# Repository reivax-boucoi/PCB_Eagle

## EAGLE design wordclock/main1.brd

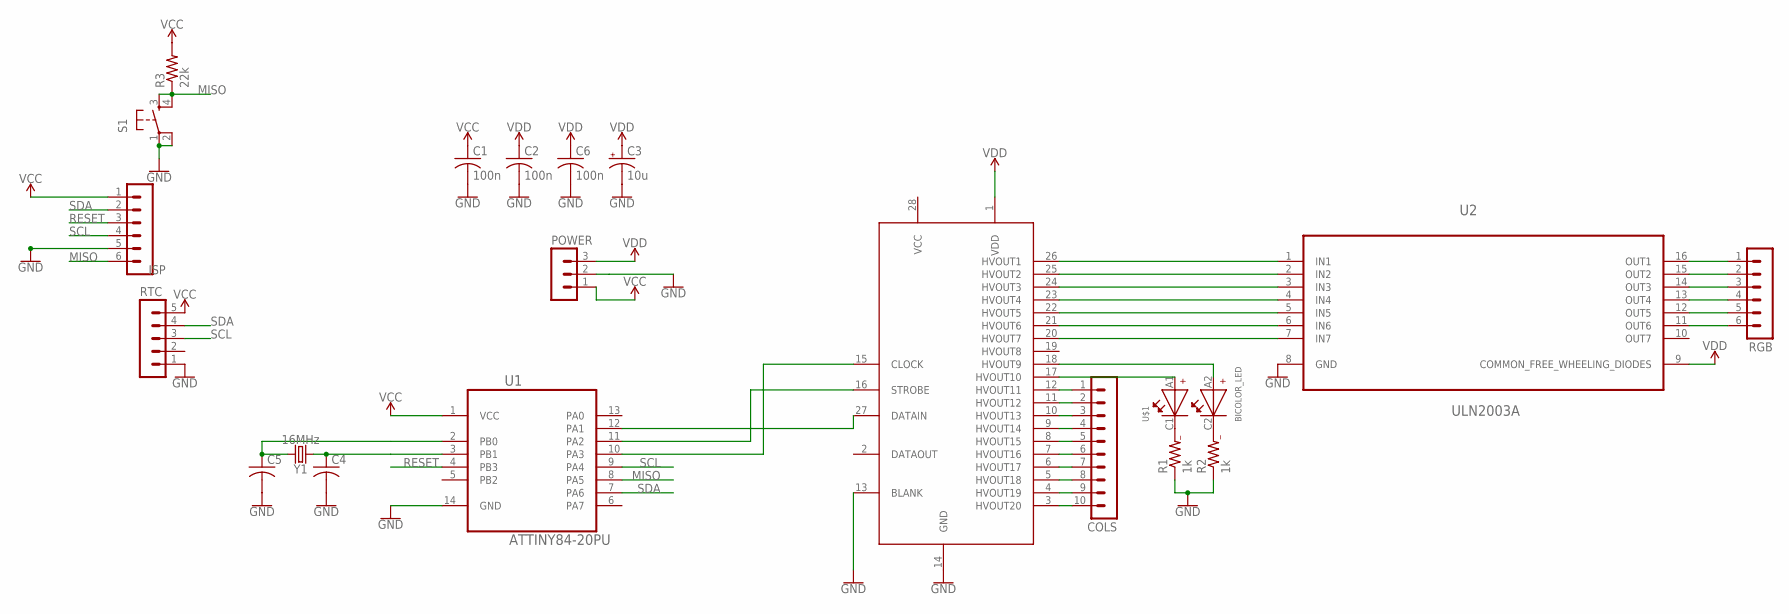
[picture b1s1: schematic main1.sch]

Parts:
C1, C2, C6: 100n; C025-025X050
C3: 10u; E2-5
C4, C5: C-USC0603K; C0603K
COLS: MA10-1W
ISP: MA06-1
POWER: MA03-1
R1, R2: 1k; R0603
R3: 22k; R0603
RGB: MA06-1
RTC: MA05-1
S1: TAC_SWITCHPTH; TACTILE-PTH
U1: ATTINY84-20PU; DIP254P762X533-14
U2: ULN2003A; DIP254P762X508-16
U$1: BICOLOR_LED
U$2: HV5812; DIP254P1524X482-28
Y1: 16MHz; HC49US

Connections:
GND: C1.2, C2.2, C3.-, C4.2, C5.2, C6.2, ISP.5, POWER.2, R1.1, R2.1, RTC.1, S1.1, S1.2, U1.14 (GND), U2.8 (GND), U$2.13 (BLANK), U$2.14 (GND)
MISO: ISP.6, R3.1, S1.3, S1.4, U1.8 (PA5)
unnamed: U2.1 (IN1), U$2.26 (HVOUT1)
unnamed: U2.2 (IN2), U$2.25 (HVOUT2)
unnamed: U2.3 (IN3), U$2.24 (HVOUT3)
unnamed: U2.4 (IN4), U$2.23 (HVOUT4)
unnamed: U2.5 (IN5), U$2.22 (HVOUT5)
unnamed: U2.6 (IN6), U$2.21 (HVOUT6)
unnamed: U2.7 (IN7), U$2.20 (HVOUT7)
unnamed: RGB.1, U2.16 (OUT1)
unnamed: RGB.2, U2.15 (OUT2)
unnamed: RGB.3, U2.14 (OUT3)
unnamed: RGB.4, U2.13 (OUT4)
unnamed: RGB.5, U2.12 (OUT5)
unnamed: RGB.6, U2.11 (OUT6)
unnamed: COLS.1, U$2.12 (HVOUT11)
unnamed: COLS.2, U$2.11 (HVOUT12)
unnamed: COLS.3, U$2.10 (HVOUT13)
unnamed: COLS.4, U$2.9 (HVOUT14)
unnamed: COLS.5, U$2.8 (HVOUT15)
unnamed: COLS.6, U$2.7 (HVOUT16)
unnamed: COLS.7, U$2.6 (HVOUT17)
unnamed: COLS.8, U$2.5 (HVOUT18)
unnamed: COLS.9, U$2.4 (HVOUT19)
unnamed: COLS.10, U$2.3 (HVOUT20)
unnamed: U$1.A1, U$2.17 (HVOUT10)
unnamed: U$1.A2, U$2.18 (HVOUT9)
unnamed: R1.2, U$1.C1
unnamed: R2.2, U$1.C2
unnamed: U1.10 (PA3), U$2.15 (CLOCK)
unnamed: U1.11 (PA2), U$2.16 (STROBE)
unnamed: U1.12 (PA1), U$2.27 (DATAIN)
PB0: C5.1, U1.2 (PB0), Y1.2
PB1: C4.1, U1.3 (PB1), Y1.1
RESET: ISP.3, U1.4 (PB3)
SCL: ISP.4, RTC.3, U1.9 (PA4)
SDA: ISP.2, RTC.4, U1.7 (PA6)
VCC: C1.1, ISP.1, POWER.1, R3.2, RTC.5, U1.1 (VCC)
VDD: C2.1, C3.+, C6.1, POWER.3, U2.9 (COMMON_FREE_WHEELING_DIODES), U$2.1 (VDD)

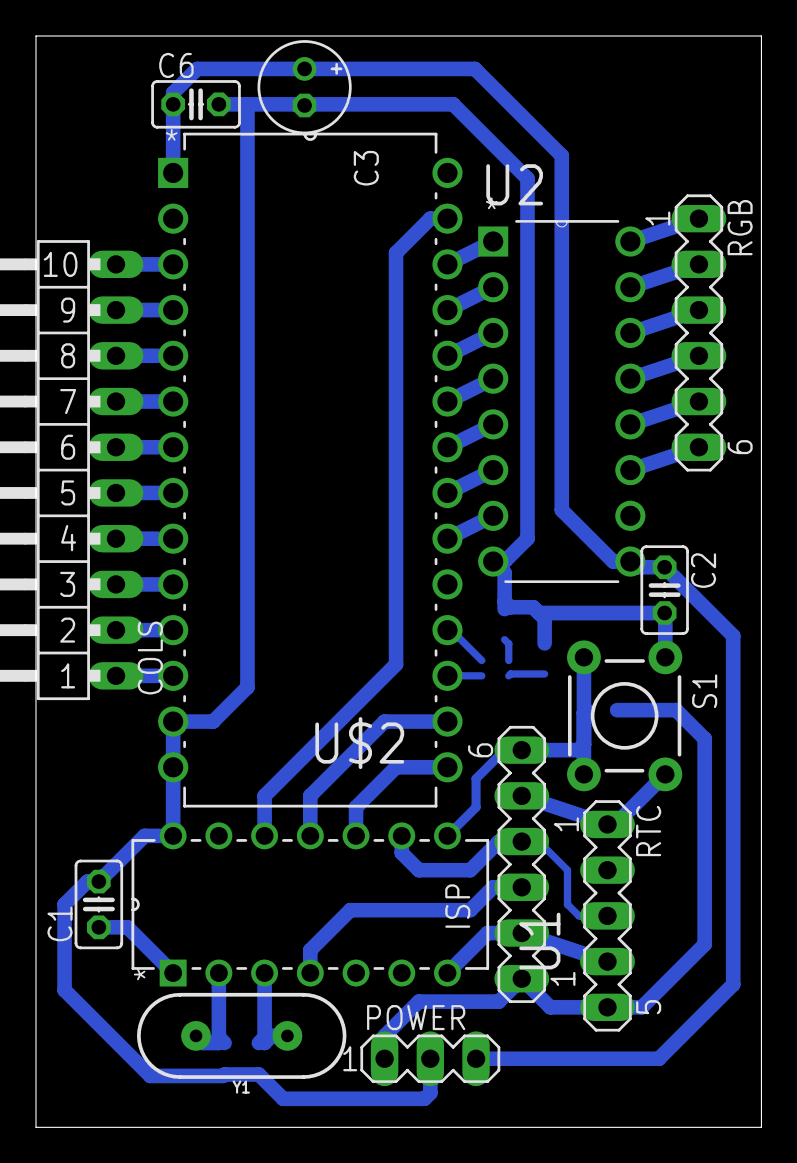
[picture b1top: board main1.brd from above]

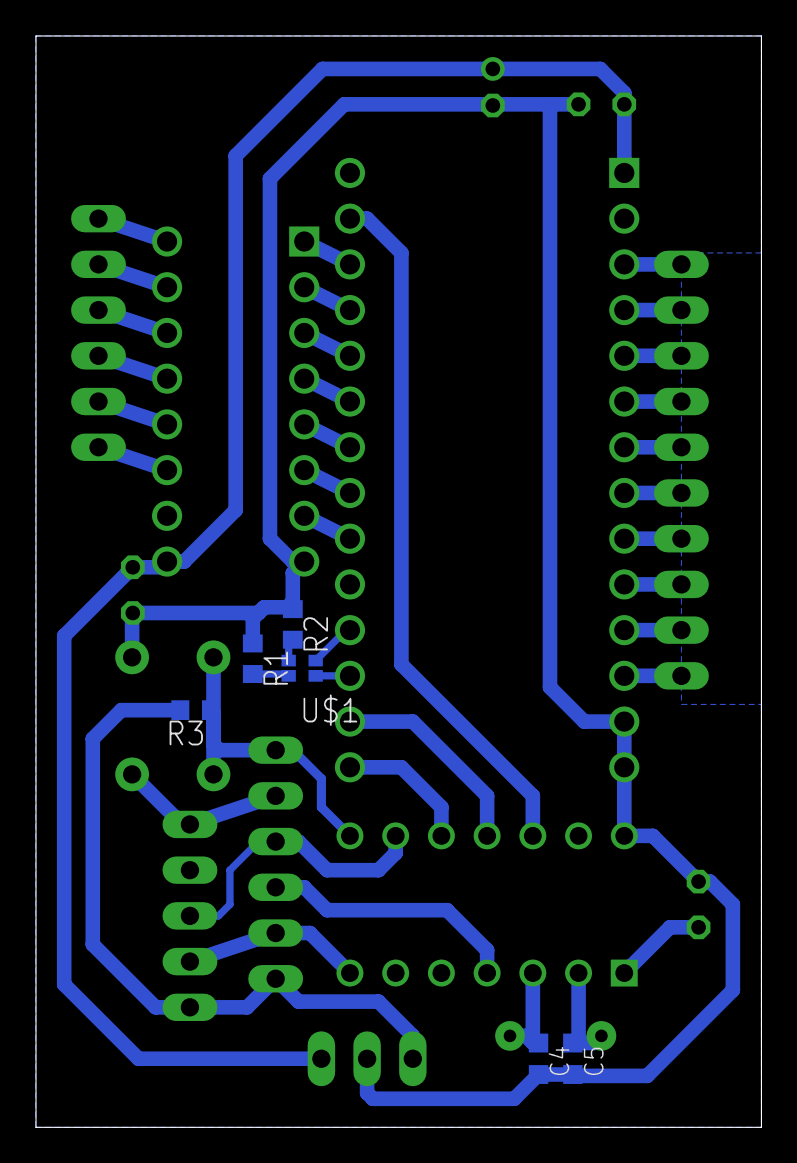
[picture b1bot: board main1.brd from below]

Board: 2 copper layers, 40.3 x 60.6 mm, 20 parts (6 on the bottom side), 39 nets.

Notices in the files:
parts and their libraries:
SparkFun-Retired: Licensing: Creative Commons ShareAlike 4.0 International - https://creativecommons.org/licenses/by-sa/4.0
